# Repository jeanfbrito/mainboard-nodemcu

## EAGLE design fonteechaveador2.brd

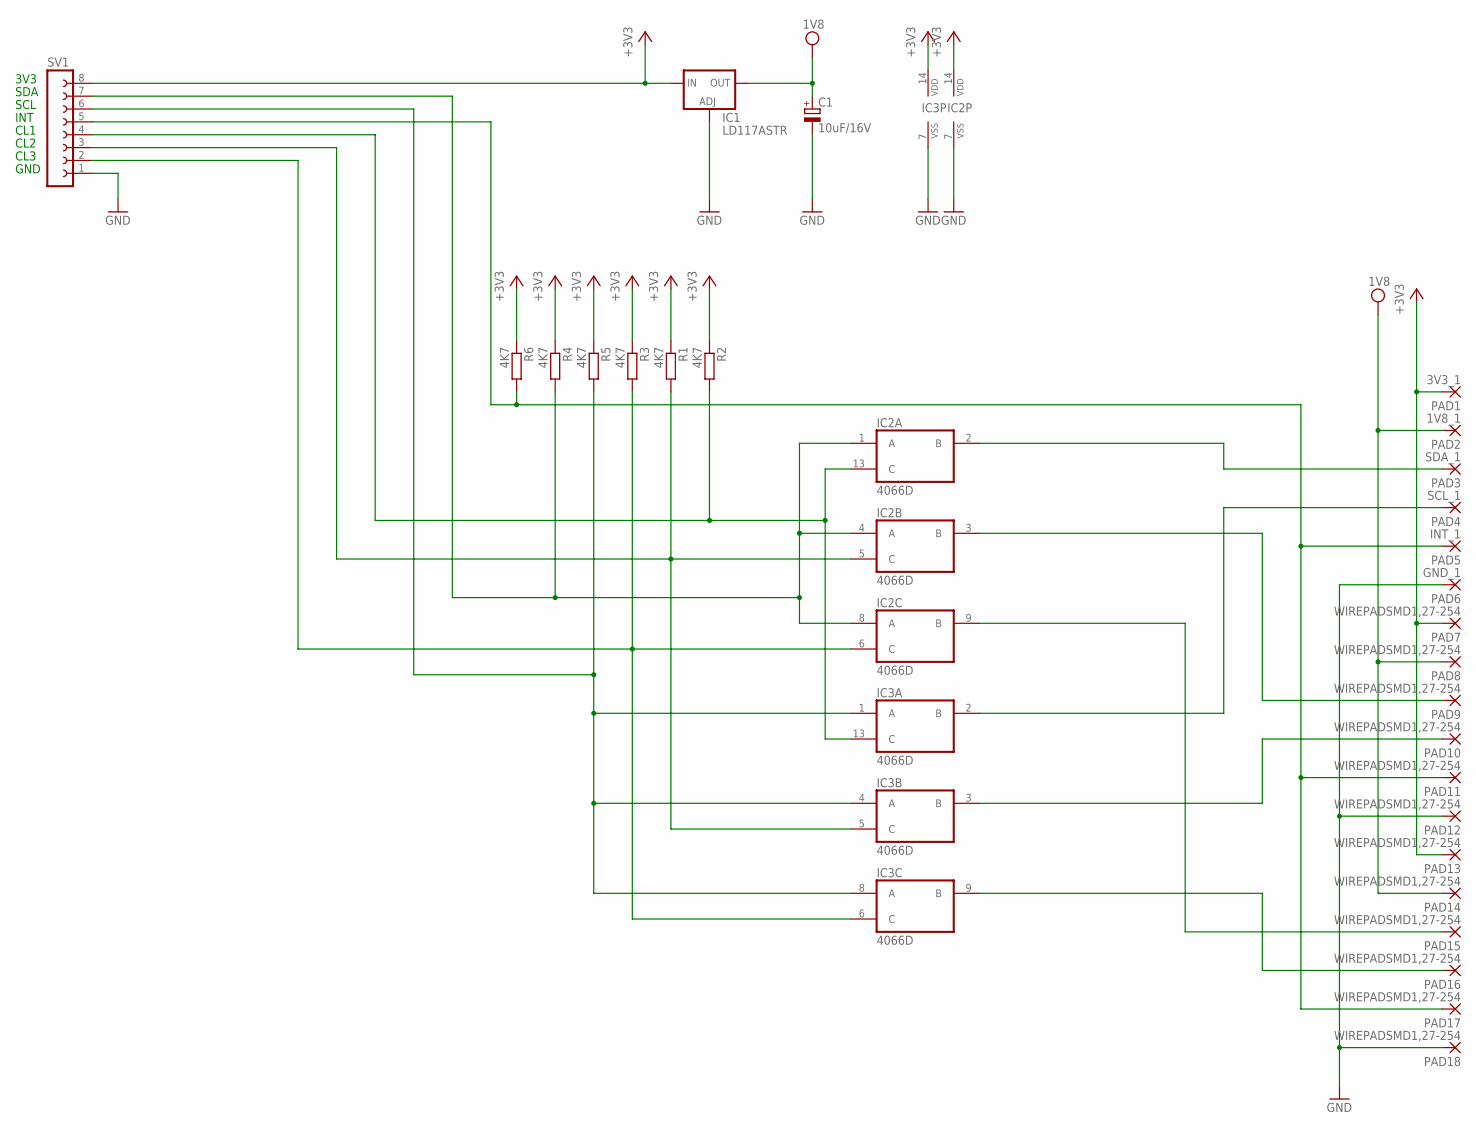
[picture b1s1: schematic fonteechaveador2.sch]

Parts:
C1: 10uF/16V; 140CLH-0810
IC1: LD117ASTR; SOT223
IC2, IC3: 4066D; SO14
PAD1: 3V3_1; SMD1,27-2,54
PAD2: 1V8_1; SMD1,27-2,54
PAD3: SDA_1; SMD1,27-2,54
PAD4: SCL_1; SMD1,27-2,54
PAD5: INT_1; SMD1,27-2,54
PAD6: GND_1; SMD1,27-2,54
PAD7, PAD8, PAD9, PAD10, PAD11, PAD12, PAD13, PAD14, PAD15, PAD16, PAD17, PAD18: WIREPADSMD1,27-254; SMD1,27-2,54
R1, R2, R3, R4, R5, R6: 4K7; M0805
SV1: FE08-1; FE08

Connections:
+3V3: IC1.3 (IN), IC2.14 (VDD), IC3.14 (VDD), PAD1.1, PAD7.1, PAD13.1, R1.1, R2.1, R3.1, R4.1, R5.1, R6.1, SV1.8
GND: C1.-, IC1.1 (ADJ), IC2.7 (VSS), IC3.7 (VSS), PAD6.1, PAD12.1, PAD18.1, SV1.1
unnamed: IC2.13 (C), IC3.13 (C), R2.2, SV1.4
unnamed: IC2.5 (C), IC3.5 (C), R1.2, SV1.3
unnamed: IC2.1 (A), IC2.4 (A), IC2.8 (A), R4.2, SV1.7
unnamed: IC3.1 (A), IC3.4 (A), IC3.8 (A), R5.2, SV1.6
unnamed: PAD5.1, PAD11.1, PAD17.1, R6.2, SV1.5
unnamed: IC2.2 (B), PAD3.1
unnamed: IC2.3 (B), PAD9.1
unnamed: IC2.9 (B), PAD15.1
unnamed: IC3.2 (B), PAD4.1
unnamed: IC3.3 (B), PAD10.1
unnamed: IC3.9 (B), PAD16.1
unnamed: IC2.6 (C), IC3.6 (C), R3.2, SV1.2
VDD: C1.+, IC1.4 (OUT), PAD2.1, PAD8.1, PAD14.1

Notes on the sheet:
3V3
SDA
SCL
CL1
CL2
CL3
GND
INT

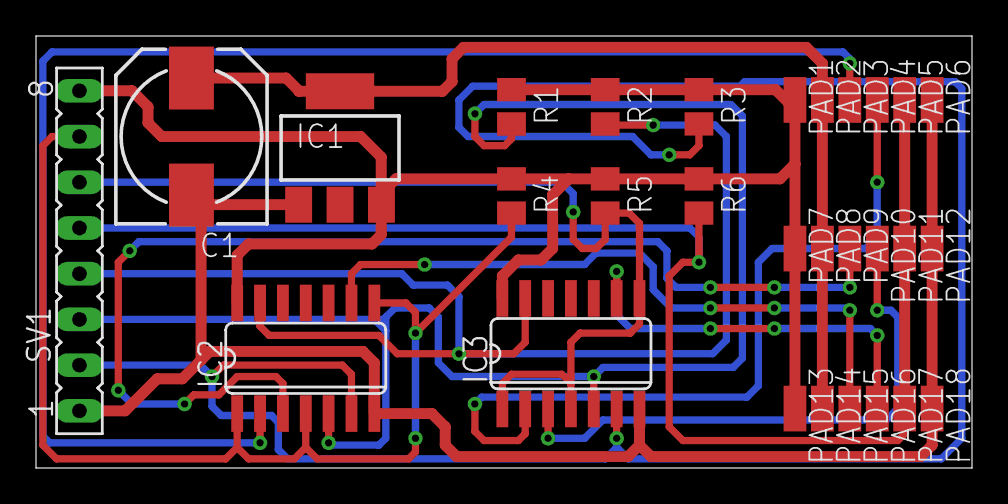
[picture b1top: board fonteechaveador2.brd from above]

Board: 2 copper layers, 52.0 x 24.0 mm, 29 parts (0 on the bottom side), 15 nets.

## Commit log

2016-10-11 :tada: Added .gitattributes & .gitignore files
